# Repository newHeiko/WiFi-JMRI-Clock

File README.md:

# WiFi-JMRI-Clock
Battery-powered WiFi device driving cheap analog wall clocks with clock information from a wiThrottle server.

It is built around ESP12E/ESP12F WiFi modules, powered by 2xAA cells and supposed to fit a Compact AA housing from New Age Enclosures. Configuration will be done through an integrated web server.

This repo contains the schematic and pcb in the hardware/ subfolder and the ESP firmware source code in the form of an Arduino sketch in the software/esp-firmware subfolder.

In-Progress-Version of documentation is available in documentation/ subfolder or at https://newHeiko.github.io/WiFi-JMRI-Clock.

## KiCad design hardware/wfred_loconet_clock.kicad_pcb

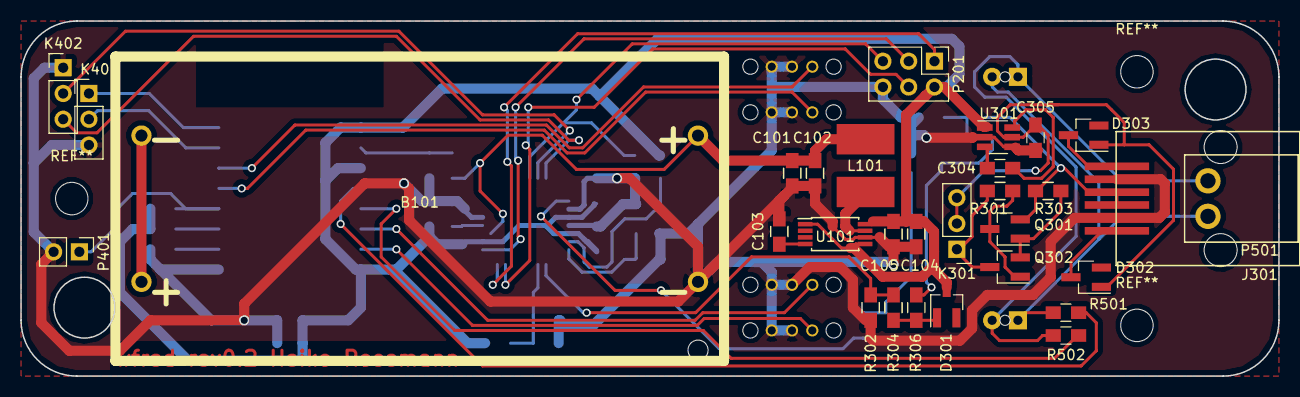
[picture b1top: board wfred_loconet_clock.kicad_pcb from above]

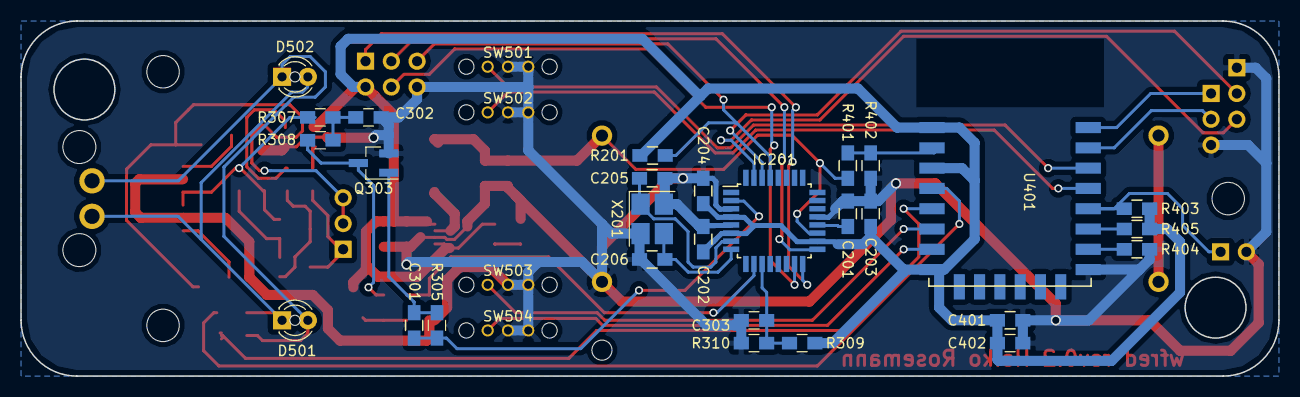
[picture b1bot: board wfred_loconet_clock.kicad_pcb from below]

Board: 2 copper layers, 124.0 x 35.0 mm, 62 parts (32 on the bottom side), 45 nets.

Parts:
B101: BATT_HOLDER; KEYSTONE1013
C101, C102, C104, C105: 22u/25V; C_0805_HandSoldering
C103, C201, C202, C203, C204, C303, C401: 100n; C_0805_HandSoldering
C205, C206: 22p; C_0805_HandSoldering
C301: 1n; C_0805_HandSoldering
C302: 47p; C_0805_HandSoldering
C304, C305, C402: 22u; C_0805_HandSoldering
D301, D302, D303: BAR43; SOT-23_Handsoldering
D501, D502: red; LED_D3.0mm
IC201: ATMEGA328P-A; TQFP-32_7x7mm_Pitch0.8mm
J301: Molex 95501-6669; Molex_95501-6669
K301: TERMINATION; Pin_Header_Straight_1x03_Pitch2.54mm
K401: UART_ESP; Pin_Header_Straight_1x03_Pitch2.54mm
K402: UART_AVR; Pin_Header_Straight_1x03_Pitch2.54mm
L101: 22u; L_2424_HandSoldering
P201: ISP; Pin_Header_Straight_2x03_Pitch2.54mm
P401: ESP_BOOTLOAD; Pin_Header_Straight_1x02_Pitch2.54mm
P501: CLOCK; AKL183-02
Q301, Q302, Q303: BC817-40; SOT-23_Handsoldering
R201, R403, R404, R405: 10k; C_0805_HandSoldering
R301: 4k7; C_0805_HandSoldering
R302, R304, R310: 47k; C_0805_HandSoldering
R303: 47R; C_0805_HandSoldering
R305: 2k2; C_0805_HandSoldering
R306: 82k; C_0805_HandSoldering
R307, R308: 12R; C_0805_HandSoldering
R309, R401, R402: 100k; C_0805_HandSoldering
R501, R502: 220; C_0805_HandSoldering
SW501, SW502, SW503, SW504: SWITCH_INV; OS102011MS2Q
U101: L6920D; TSSOP-8_4.4x3mm_Pitch0.65mm
U301: TC1240; SOT-23-6_Handsoldering
U401: ESP-12E; ESP-12E_SMD
X201: myCRYSTAL; Crystal_SMD_TXC_7M-4pin_3.2x2.5mm_HandSoldering

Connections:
+5V: C305.1, D302.1, D303.1, K301.2, K301.3, U301.5
+BATT: B101.PL1, C101.1, C102.1, IC201.19, L101.1, R401.1
CLOCK1: R501.2, U401.4
CLOCK2: R502.2, U401.5
ESTOP: IC201.15, P201.4
GND: B101.MI2, C101.2, C102.2, C103.2, C104.2, C105.2, C201.2, C202.2, C203.2, C204.2, C205.2, C206.2, C302.2, C303.2, C305.2, C401.2, C402.2, IC201.3, IC201.5, IC201.21, J301.2, J301.5, K401.3, K402.1, P201.6, P401.2, Q303.2, R302.1, R310.2, R402.2, R404.1, SW501.1, SW501.2, SW502.1, SW502.2, SW503.1, SW503.2, SW504.1, SW504.2, U101.6, U301.2, U301.4, U401.9, X201.2, X201.4
LN_RX0: IC201.10, R302.2, R304.2
LN_RX1: C303.1, IC201.11, R309.2, R310.1
LN_RXTX: J301.3, J301.4, Q301.2, R303.1, R307.1
LN_TX: C301.2, IC201.2, R305.2
LOCO1: SW501.3, U401.14
LOCO2: SW502.3, U401.13
LOCO3: SW503.3, U401.6
LOCO4: SW504.3, U401.7
MISO: IC201.16, P201.1
unnamed: B101.MI1, B101.PL2
unnamed: C103.1, U101.4
unnamed: C201.1, IC201.20
unnamed: C205.1, IC201.7, X201.1
unnamed: C206.1, IC201.8, X201.3
unnamed: C301.1, Q303.1, R305.1
unnamed: C302.1, R307.2, R308.1
unnamed: C304.1, U301.6
unnamed: C304.2, U301.3
unnamed: D301.1, R304.1, R306.2
unnamed: D302.3, J301.1
unnamed: D303.3, J301.6
unnamed: D501.1, D502.2, P501.1, R501.1
unnamed: D501.2, D502.1, P501.2, R502.1
unnamed: K301.1, Q302.3, R301.2
unnamed: K401.1, U401.16
unnamed: K401.2, U401.15
unnamed: L101.2, U101.7
unnamed: P401.1, R403.1, U401.12
unnamed: Q301.1, Q302.2, R303.2
unnamed: Q301.3, Q302.1, R301.1
unnamed: Q303.3, R306.1, R308.2
unnamed: R401.2, R402.1, U401.2
unnamed: R404.2, U401.10
unnamed: R405.1, U401.11
RESET: IC201.29, P201.5, R201.2
SCK: IC201.17, P201.3
THIS_RXD: IC201.30, K402.2
THIS_TXD: IC201.31, K402.3
VCC: C104.1, C105.1, C202.1, C203.1, C204.1, C401.1, C402.1, D301.3, IC201.4, IC201.6, IC201.18, P201.2, R201.1, R309.1, R403.2, R405.2, U101.1, U101.5, U101.8, U301.1, U401.1, U401.3, U401.8

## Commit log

2019-02-12 Removed wiFred info from from clock project
2019-02-12 README update
2019-02-12 Untangle throttle functions from WiFi-JMRI-Clock
2019-02-13 Fix schematic after untangling from wiFred
2019-02-13 Fixed PCB after untangling
2019-03-07 Change project info in source files
    - project description from throttle to clock
    - project build info
2019-03-07 Add new input button and led handling code
    ...and replace calls to removed code with calls to new code, as well as
    add calls to LED settings
2019-03-07 Re-work battery status management
    - Re-add old battery voltage measurement code
    - Handle empty battery status unconditionally in main loop, getting rid
    of LOW_POWER* states
2019-03-07 Use proper data types for sscanf
2019-03-07 Remove clockActive setting
2019-03-07 Remove unused functions
2019-03-08 Change clock schematic and PCB
    - Remove slide switches, replace with single push button
    - Add status LED
    - Re-add battery measurement connection
    - Change PCB form factor to fit NewAgeEnclosures Compact AA housing
    - Re-layout PCB
2019-03-10 Changed PCB and code to closer match first PCB
    - Add battery measurement resistors
    - Move key, status LED and clock I/O-pins around to match first PCB
    (except for CLOCK1 which is on low power pin in first version)
2019-03-10 On the old PCB, CLOCK1 pin is on I/O-pin 4
    ...change firmware accordingly
2019-03-10 Use sliding switch status to switch to config mode
    ...instead of pushbutton was pressed information
2019-03-11 Change wording from wiFred to wiClock...
    ...and also switch Arduino.h for ESP8266WiFi.h include and change LED
    blink code for CONFIG_AP
2019-03-11 Correct clock, led and input switch pin associations
2019-03-11 Add forgotten call to lowBatteryHandler in main
2019-04-07 Added more keys to the PCB for adjusting the time
2019-04-20 Changes to kicad files due to library update/rescue
2019-04-20 Extend ESP firmware to handle four keys
    - so far only KEY_CONFIG actually used
2019-04-21 Reformat file
2019-04-21 Add catch-all-DNS-server to config-AP-mode
2019-04-21 Revert "Add catch-all-DNS-server to config-AP-mode"
    This reverts commit fd152f8f4f9196d7bcbb3e4bec8e7f7e90fd10e0.
2019-05-12 Derive default device name from MAC address
2019-05-12 Add DNS server and mDNS responder
    - catchall DNS server for "captive mode" when device is running as softAP
    - mDNS responder when connected to WiFi in "normal mode" will broadcast
    http service as <throttleName>.local (sanitized, only alpha-numeric
    characters allowed)
    - mDNS responder when connected to WiFi in "config mode" will broadcast
    http service config.local
2019-05-12 Add http firmware updater
2019-05-12 Remove old hostname service when restarting
2019-05-12 When losing connection during configuration mode...
    ...restart WiFi
2019-05-12 Adapt to debugging on NodeMCU
    - set DEBUG defines
    - disable shutdown on low battery
    - change pin and LED settings to match NodeMCU hardware
2019-05-12 Revert "Adapt to debugging on NodeMCU"
    This reverts commit 105eb5fb26e527b0c10b249fa7aa00d5727972b6.
2019-05-24 Move Serial startup before config init...
    ...to allow for debugging in initConfig and initClock
2019-05-24 May not compile: Moved configuration to SPIFFS...
    ...from EEPROM
    - Also re-jiggled configuration websites
    - Also allowed for more granular configuration saving
2019-05-24 Add scanning for WiFi networks
2019-05-24 Add automatic clock server found through mDNS...
    ...any server announcing _http._tcp on port 12080 (or whatever is
    configured in the web interface)
2019-05-24 Modified mDNS service announcements...
    ...for configuration mode and for normal mode
2019-07-01 Carry over missing .html bugfix from wiFred
2019-07-28 Add TODO file with notes from large test meeting...
    ...around 2019-07-27
2019-08-02 Add second clock output...
    ...while removing (so far) unused key
2019-08-03 Add a shell script and a dummy file to get git rev
    Stored in a #define named REV
2019-08-04 Fixed missing GND connection on PCB...
    ...found during order process.
2019-08-27 Add a BOM file for wiClock 1.0
2019-11-08 Update Partlist to currently available parts
2019-11-08 Begin rework to support v1.0-version
    - Add second clock info structure
    - Handle three keys instead of four
    - Add defines for second clock output
2019-11-10 WIP: Handle more than one clock
    - Added clockInfo fields
    - Removed global variables
    - Changed ticker callbacks to accept arguments
    TBD: Correct newTime handling in clockHandler()
    TBD: Add second clock to web server page
2019-11-12 WIP: Handle more than one clock
    - Handle newTime for both clocks in clockHandler()
    TBD: Add second clock to web server page
2019-11-12 Handle more than one clock
    - Add second clock output to web server page
    - Reorder web server page
    - WIP: Add stub for setting time from web server page
2019-11-12 Finish setting time through web page stub
2019-11-12 Add handling of hour and minute input switches
    BUG: Ignores hour switch
2019-11-12 Bugfix: Include KEY_HOUR in key handling
2019-11-12 Bugfix: Roll-under from 00:xx:xx to 11:xx:xx
    ...instead of %= 12 leading to 03:xx:xx
2019-11-12 Move "wiClock configuration page" headline...
    ...back to top of web page where it belongs
2019-11-13 Add current firmware revision info...
    ...from git
2019-12-30 Corrected AKL 183-02 / AKL 169-02 to include both
    ...numbers in BOM.
2020-02-09 Updated part list
2020-02-09 Opened schematic and pcb with kicad 5.1.5...
    ...to update library table
2020-04-20 Added second clock and switched to minute mode
    Also consolidated configuration and changed catch-up behaviour to slow
    down when closing in on correct time.
2021-01-30 Fixed up wfred_loconet_clock PCB...
    ...just in case someone actually wants to use it...
2021-12-26 Some doc reorganization
2021-12-26 Reorganize esp-firmware naming
2021-12-26 Complete renaming of firmware
2021-12-26 Update copyright notices to 2021 and wiClock
2021-12-26 Re-add file missing after reorganizing folder
2021-12-26 Remove unused defines
2021-12-26 Fix a bunch of warnings
    - Warnings about wrong char[] length calculation -> switch char[] to String
    - Suppress deprecated warnings for SPIFFS
2021-12-26 Fix string length warnings
    - just increase buffer size, even though hours/minutes/seconds are all
    limited to two digits, can't find out how to tell GCC that
2021-12-27 Update WiFi settings page
    - hide PSK
    - add option to disable WiFi networks
2021-12-27 Remove clock offset from UTC
    ...in preparation to switching to wiThrottle server as clock source.
2021-12-27 Switch port and MDNS service to withrottle server
2021-12-27 Re-organize states for constant connection
    - also actually ignore disabled networks
2022-01-09 Switched over to constant wiThrottle connection
    - Added state transitions
2022-01-09 Reorganize web page to match wiFred webpage
2022-01-16 Switched from bool minuteMode to enum clockMode
    ...to support more modes for sweeping clocks.
    So far, only minute mode and second mode work right.
2022-01-16 Handle different clock modes
    Still have to find a clock that will work nicely with anything but
    CLOCK_MODE_SECOND, but...
2022-03-14 Remove old documentation taken over from wiFred
2022-03-14 Switch file names to English
2022-03-14 Documentation abstract.
2022-03-14 Correct github pages forwarding
2022-03-15 Documentation update: Usage, LED, pushbuttons
2022-03-15 Actually use both startupTimes
2022-03-15 Removed trailing underscore -> fix github pages?
2023-10-08 Add board configuration for IniIno into sketch
    Get it here: https://github.com/tykefcz/IniIno
2023-10-08 Set DHCP hostname before starting WiFi network
